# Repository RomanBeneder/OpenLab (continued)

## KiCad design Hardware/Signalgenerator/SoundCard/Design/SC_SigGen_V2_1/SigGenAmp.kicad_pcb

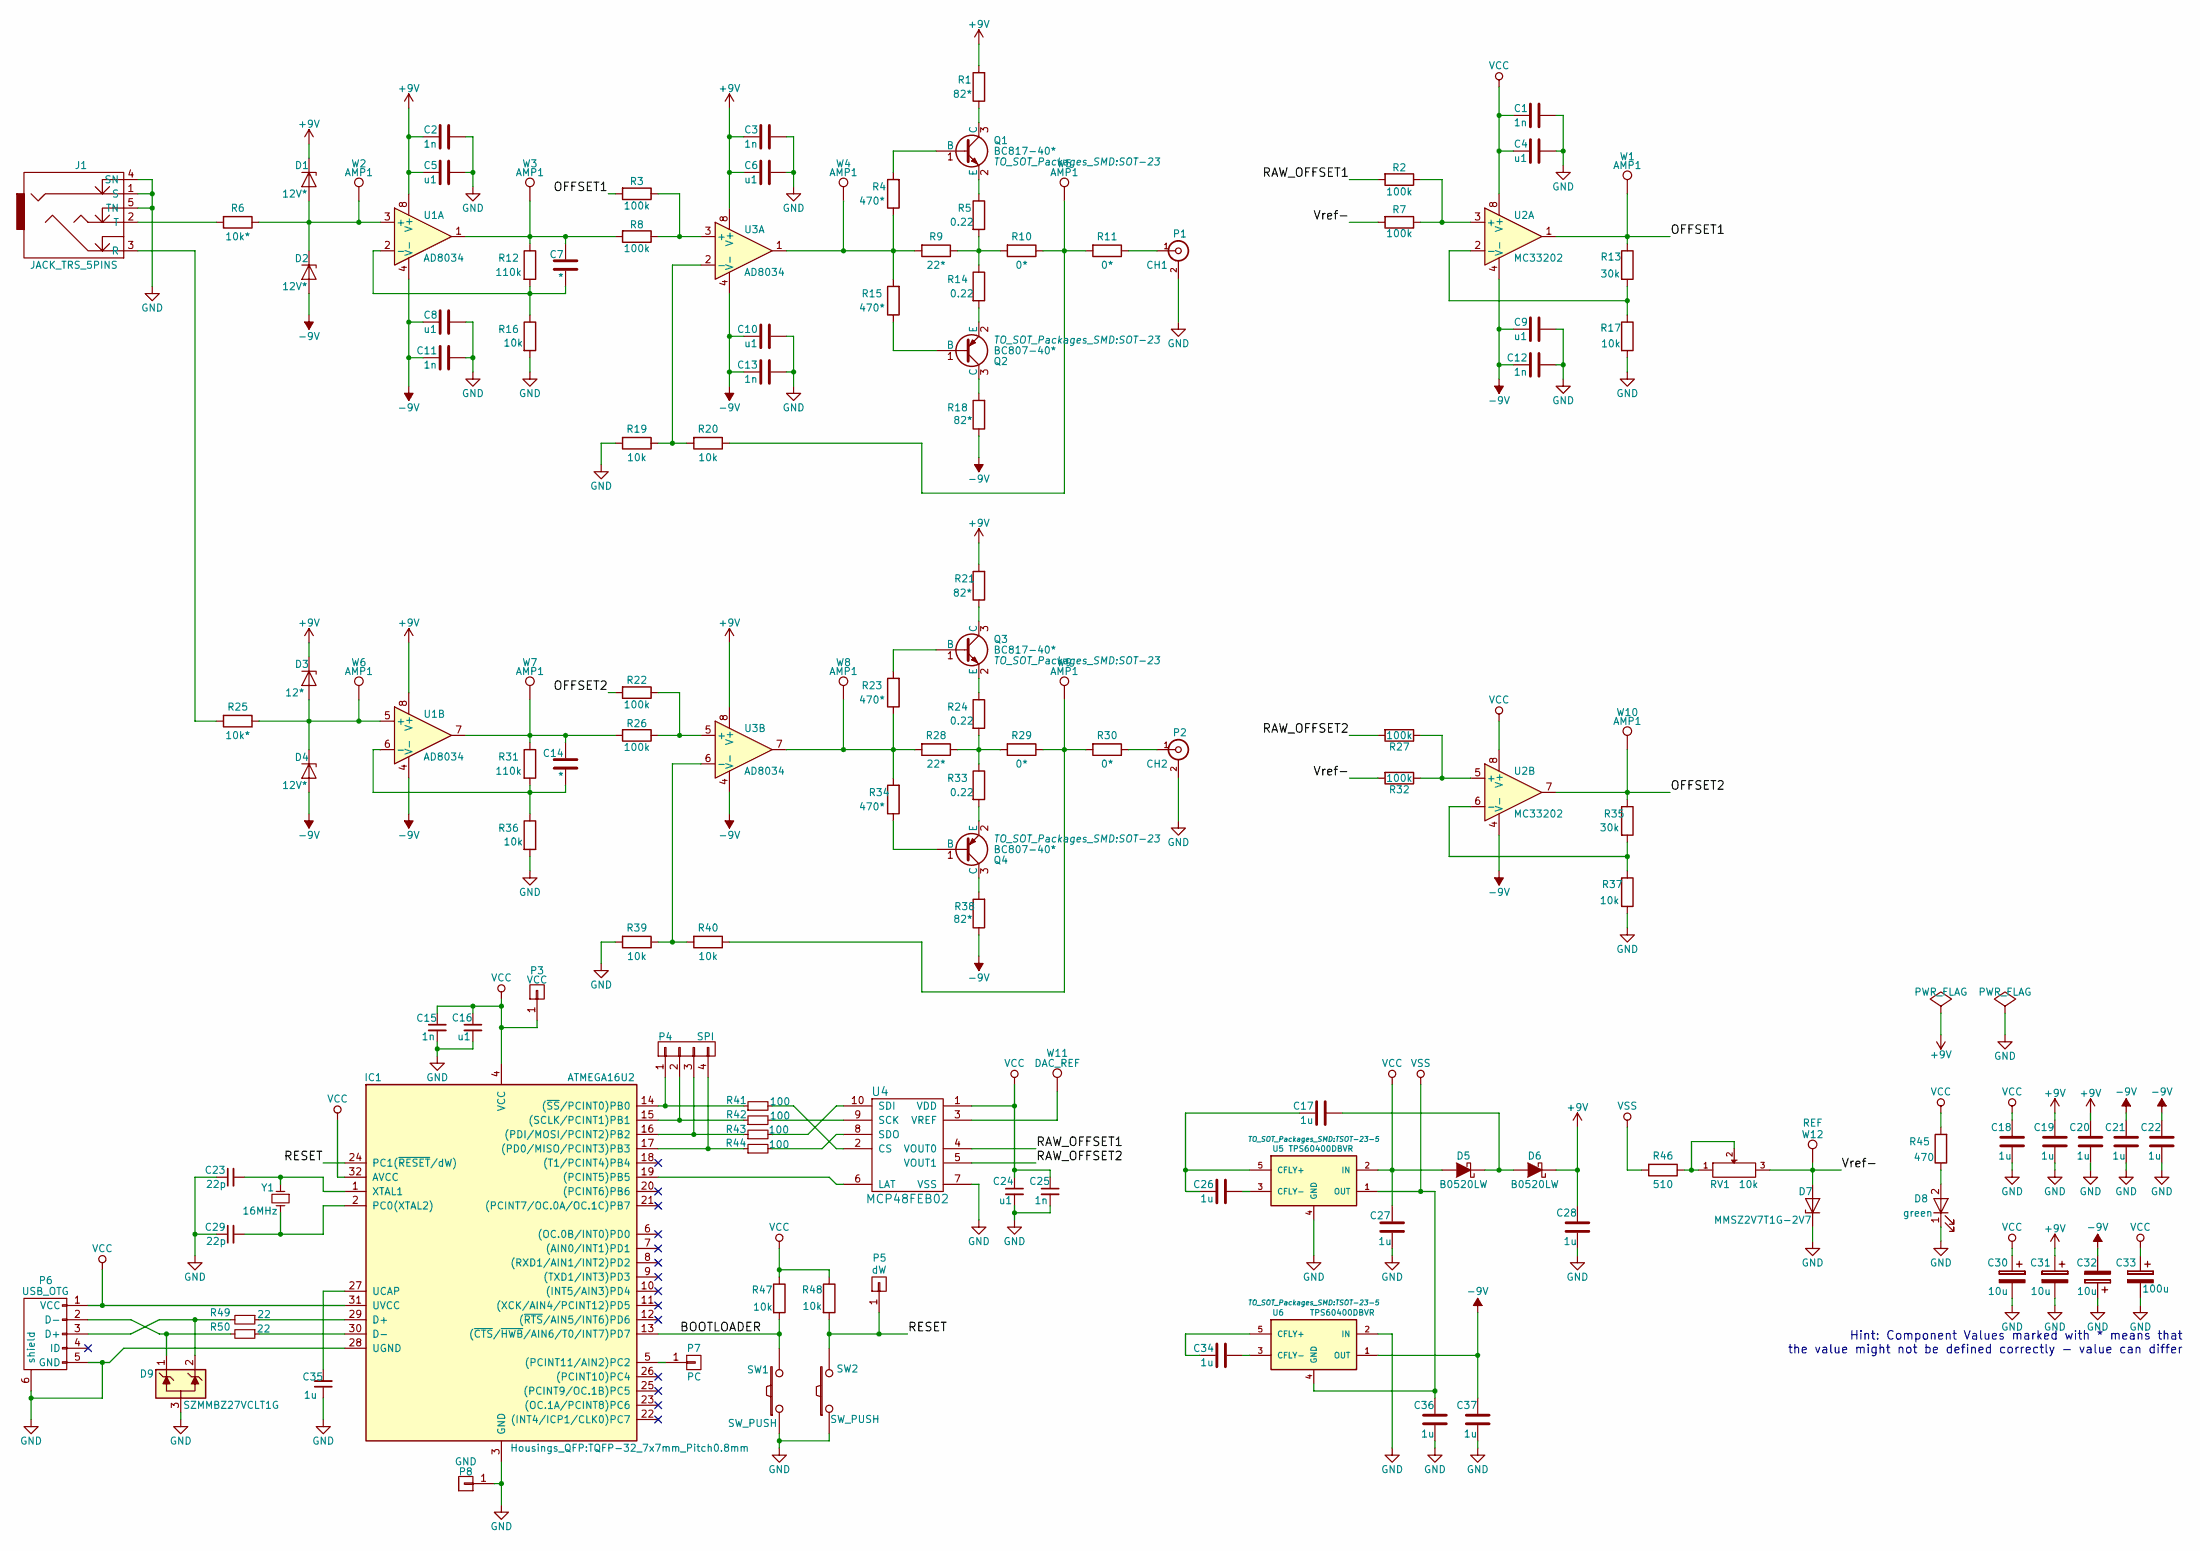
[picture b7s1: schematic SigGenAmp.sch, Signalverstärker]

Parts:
C1, C2, C3, C11, C12, C13, C15, C25: 1n; C_0603
C4, C5, C6, C8, C9, C10, C16, C24: u1; C_0603
C7, C14: *; C_0603
C17, C18, C19, C20, C21, C22, C26, C27, C28, C34, C35, C36, C37: 1u; C_0603
C23, C29: 22p; C_0603
C30, C31, C32: 10u; CP_Elec_4x5.8
C33: 100u; CP_Elec_6.3x7.7
D1, D2, D4: 12V*; D_SOD-323
D3: 12*; D_SOD-323
D5, D6: B0520LW; D_SOD-123
D7: MMSZ2V7T1G-2V7; D_SOD-323F
D8: green; LED_0603
D9: SZMMBZ27VCLT1G; SOT-23
IC1: ATMEGA16U2; TQFP-32_7x7mm_Pitch0.8mm
J1: JACK_TRS_5PINS; TRS3.5mm5PIN
P1: CH1; BNC_Socket_TYCO-AMP_FIX
P2: CH2; BNC_Socket_TYCO-AMP_FIX
P3: VCC; Pin_Header_Straight_1x01_Pitch2.54mm
P4: SPI; Pin_Header_Straight_1x04_Pitch2.54mm
P5: dW; Pin_Header_Straight_1x01_Pitch2.54mm
P6: USB_OTG; USB_Micro-B_SMD
P7: PC; Pin_Header_Straight_1x01_Pitch2.54mm
P8: GND; Pin_Header_Straight_1x01_Pitch2.54mm
Q1, Q3: BC817-40*; SOT-23
Q2, Q4: BC807-40*; SOT-23
R1, R18, R21, R38: 82*; R_1206
R2, R3, R7, R8, R22, R26, R27, R32: 100k; R_0603
R4, R15, R23, R34: 470*; R_0603
R5, R14, R24, R33: 0.22; R_1206
R6, R25: 10k*; R_0603
R9, R28: 22*; R_1206
R10, R11, R29, R30: 0*; R_0603
R12, R31: 110k; R_0603
R13, R35: 30k; R_0603
R16, R17, R19, R20, R36, R37, R39, R40, R47, R48: 10k; R_0603
R41, R42, R43, R44: 100; R_0603
R45: 470; R_0603
R46: 510; R_0603
R49, R50: 22; R_0603
RV1: 10k; Potentiometer_Trimmer-EVM3E
SW1, SW2: SW_PUSH; SW_SPST_PTS645
U1, U3: AD8034; SOIC-8_3.9x4.9mm_Pitch1.27mm
U2: MC33202; SOIC-8_3.9x4.9mm_Pitch1.27mm
U4: MCP48FEB02; MSOP-10_3x3mm_Pitch0.5mm
U5, U6: TPS60400DBVR; TSOT-23-5
W1, W2, W3, W4, W5, W6, W7, W8, W9, W10: AMP1; Measurement_Point_Square-SMD-Pad_Small
W11: DAC_REF; Measurement_Point_Square-SMD-Pad_Small
W12: REF; Measurement_Point_Square-SMD-Pad_Small
Y1: 16MHz; Crystal_SMD_HC49-SD

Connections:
+9V: C2.2, C3.2, C5.2, C6.2, C19.2, C20.2, C28.2, C31.1, D1.1 (K), D3.1 (K), D6.1 (K), R1.2, R21.2, U1.8 (V+), U3.8 (V+)
-9V: C8.2, C9.2, C10.2, C11.2, C12.2, C13.2, C21.2, C22.2, C32.2, C37.2, D2.2 (A), D4.2 (A), R18.1, R38.1, U1.4 (V-), U2.4 (V-), U3.4 (V-), U6.1 (OUT)
/BOOTLOADER: IC1.13 ((~CTS~/~HWB~/AIN6/T0/INT7)PD7), R47.2, SW1.2
/OFFSET1: R3.2, R13.1, U2.1, W1.1
/OFFSET2: R22.2, R35.1, U2.7, W10.1
/RAW_OFFSET1: R2.2, U4.4 (VOUT0)
/RAW_OFFSET2: R27.2, U4.5 (VOUT1)
/RESET: IC1.24 (PC1(~RESET~/dW)), P5.1, R48.2, SW2.2
/Vref-: D7.2 (A), R7.2, R32.2, RV1.3, W12.1
GND: C1.1, C2.1, C3.1, C4.1, C5.1, C6.1, C8.1, C9.1, C10.1, C11.1, C12.1, C13.1, C15.2, C16.2, C18.1, C19.1, C20.1, C21.1, C22.1, C23.1, C24.2, C25.2, C27.1, C28.1, C29.1, C30.2, C31.2, C32.1, C33.2, C35.1, C36.1, C37.1, D7.1 (K), D8.1 (K), D9.3 (A), IC1.3 (GND), IC1.28 (UGND), J1.1 (S), J1.4 (SN), J1.5 (TN), P1.2 (Ext), P2.2 (Ext), P6.5 (GND), P6.6 (shield), P8.1, R16.2, R17.2, R19.2, R36.2, R37.2, R39.2, SW1.1, SW2.1, U4.7 (VSS), U5.4 (GND), U6.2 (IN)
unnamed: C7.1, R12.2, R16.1, U1.2 (-)
unnamed: C7.2, R8.2, R12.1, U1.1, W3.1
unnamed: C14.1, R31.2, R36.1, U1.6 (-)
unnamed: C14.2, R26.2, R31.1, U1.7, W7.1
unnamed: C17.1, D5.1 (K), D6.2 (A)
unnamed: C17.2, C26.2, U5.5 (CFLY+)
unnamed: C23.2, IC1.1 (XTAL1), Y1.1
unnamed: C26.1, U5.3 (CFLY-)
unnamed: C29.2, IC1.2 (PC0(XTAL2)), Y1.2
unnamed: C34.1, U6.3 (CFLY-)
unnamed: C34.2, U6.5 (CFLY+)
unnamed: C35.2, IC1.27 (UCAP)
unnamed: D1.2 (A), D2.1 (K), R6.1, U1.3 (+), W2.1
unnamed: D3.2 (A), D4.1 (K), R25.1, U1.5 (+), W6.1
unnamed: D8.2 (A), R45.1
unnamed: D9.1 (K), P6.2 (D-), R50.2
unnamed: D9.2 (K), P6.3 (D+), R49.2
unnamed: IC1.5 ((PCINT11/AIN2)PC2), P7.1
unnamed: IC1.14 ((~SS~/PCINT0)PB0), P4.1, R41.1
unnamed: IC1.15 ((SCLK/PCINT1)PB1), P4.2, R42.1
unnamed: IC1.16 ((PDI/MOSI/PCINT2)PB2), P4.3, R43.1
unnamed: IC1.17 ((PD0/MISO/PCINT3)PB3), P4.4, R44.1
unnamed: IC1.19 ((PCINT5)PB5), U4.6 (LAT)
unnamed: IC1.29 (D+), R49.1
unnamed: IC1.30 (D-), R50.1
unnamed: J1.2 (T), R6.2
unnamed: J1.3 (R), R25.2
unnamed: P1.1 (In), R11.1
unnamed: P2.1 (In), R30.1
unnamed: Q1.1 (B), R4.2
unnamed: Q1.2 (E), R5.1
unnamed: Q1.3 (C), R1.1
unnamed: Q2.1 (B), R15.1
unnamed: Q2.2 (E), R14.2
unnamed: Q2.3 (C), R18.2
unnamed: Q3.1 (B), R23.2
unnamed: Q3.2 (E), R24.1
unnamed: Q3.3 (C), R21.1
unnamed: Q4.1 (B), R34.1
unnamed: Q4.2 (E), R33.2
unnamed: Q4.3 (C), R38.2
unnamed: R2.1, R7.1, U2.3 (+)
unnamed: R3.1, R8.1, U3.3 (+)
unnamed: R10.1, R11.2, R20.1, W5.1
unnamed: R5.2, R9.1, R10.2, R14.1
unnamed: R13.2, R17.1, U2.2 (-)
unnamed: R4.1, R9.2, R15.2, U3.1, W4.1
unnamed: R19.1, R20.2, U3.2 (-)
unnamed: R22.1, R26.1, U3.5 (+)
unnamed: R23.1, R28.2, R34.2, U3.7, W8.1
unnamed: R24.2, R28.1, R29.2, R33.1
unnamed: R27.1, R32.1, U2.5 (+)
unnamed: R29.1, R30.2, R40.1, W9.1
unnamed: R35.2, R37.1, U2.6 (-)
unnamed: R39.1, R40.2, U3.6 (-)
unnamed: R41.2, U4.2 (CS)
unnamed: R42.2, U4.9 (SCK)
unnamed: R43.2, U4.10 (SDI)
unnamed: R44.2, U4.8 (SDO)
unnamed: R46.1, RV1.1, RV1.2
unnamed: U4.3 (VREF), W11.1
VCC: C1.2, C4.2, C15.1, C16.1, C18.2, C24.1, C25.1, C27.2, C30.1, C33.1, D5.2 (A), IC1.4 (VCC), IC1.31 (UVCC), IC1.32 (AVCC), P3.1, P6.1 (VCC), R45.2, R47.1, R48.1, U2.8 (V+), U4.1 (VDD), U5.2 (IN)
VSS: C36.2, R46.2, U5.1 (OUT), U6.4 (GND)

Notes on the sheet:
Hint: Component Values marked with * means that the value might not be defined correctly - value can differ

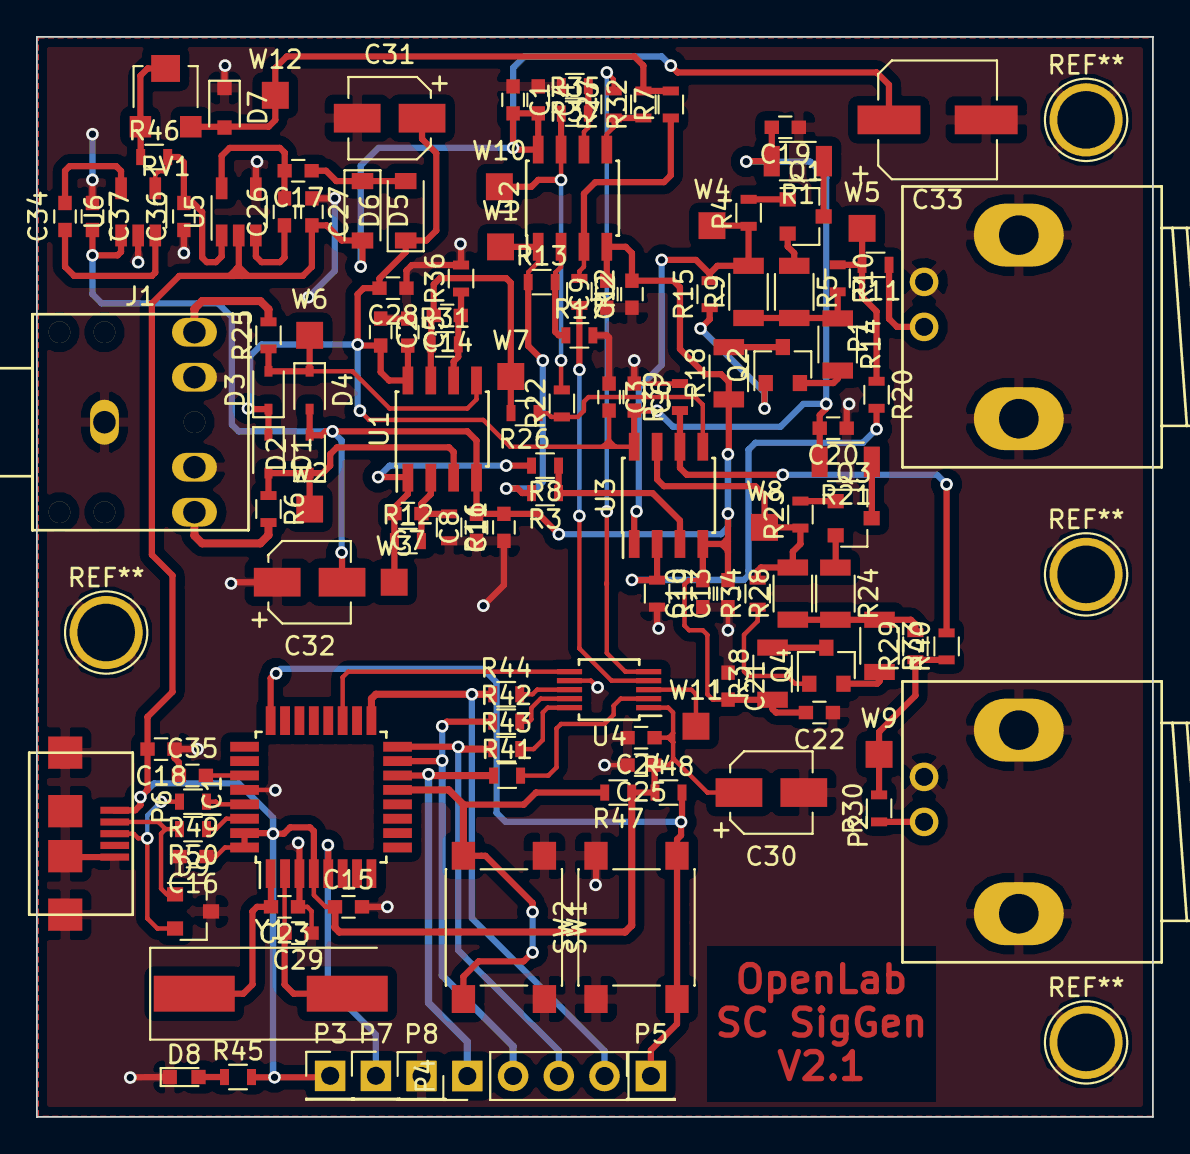
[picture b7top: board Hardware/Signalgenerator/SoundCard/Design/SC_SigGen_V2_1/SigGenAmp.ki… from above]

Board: 2 copper layers, 62.0 x 60.0 mm, 132 parts (0 on the bottom side), 73 nets.

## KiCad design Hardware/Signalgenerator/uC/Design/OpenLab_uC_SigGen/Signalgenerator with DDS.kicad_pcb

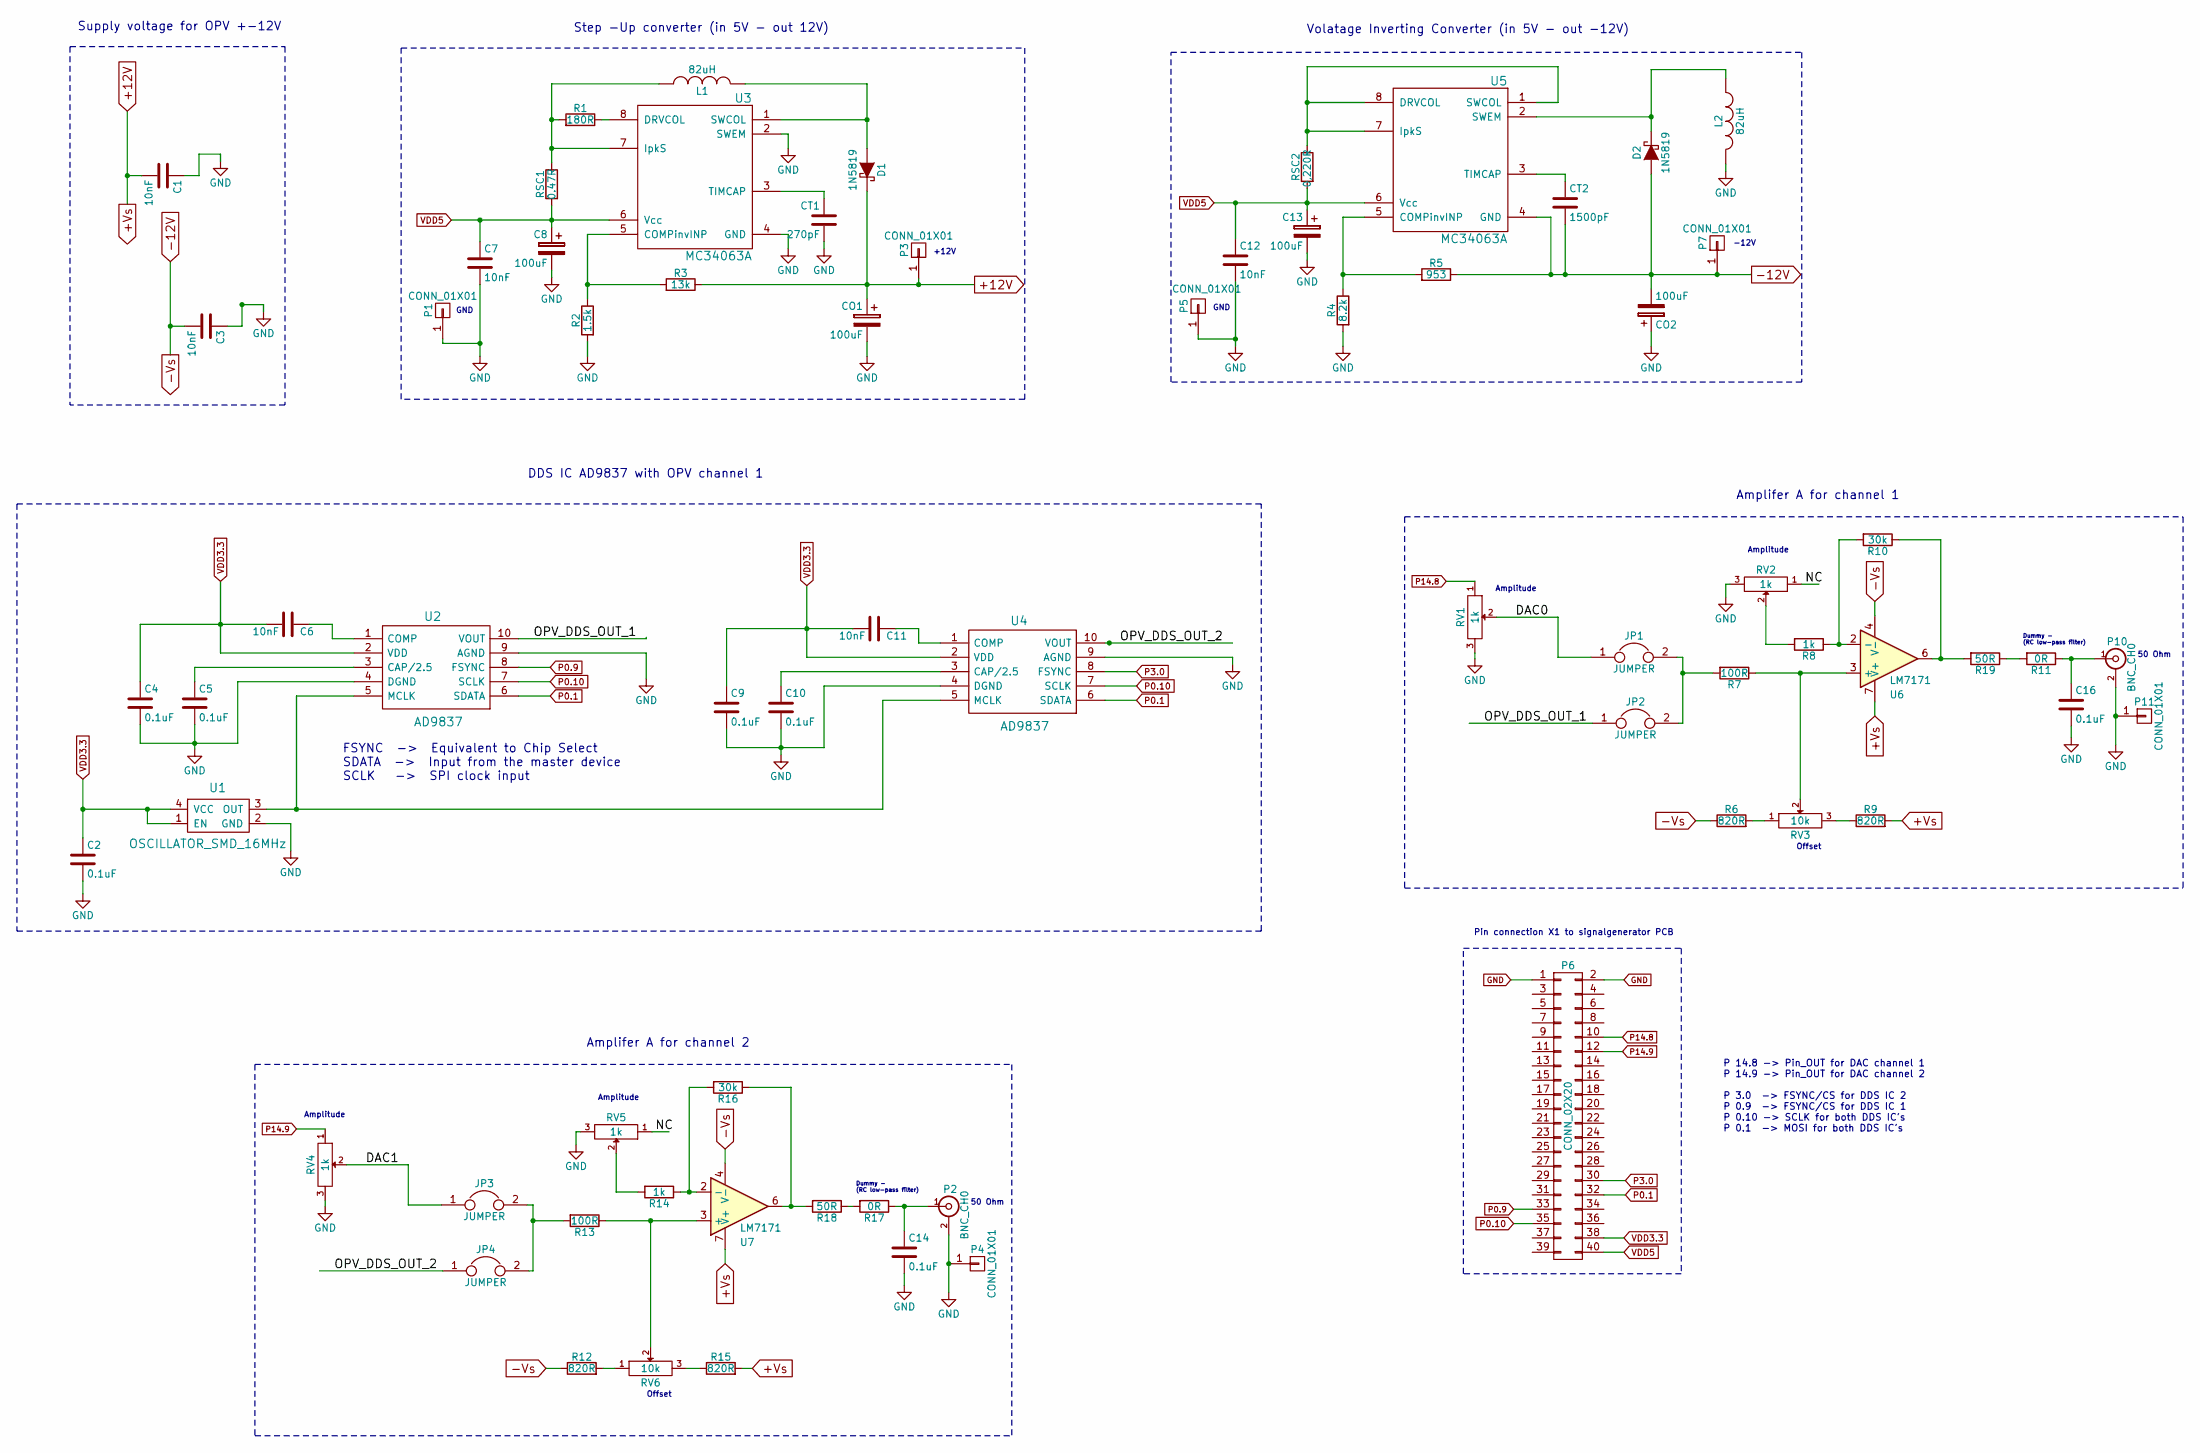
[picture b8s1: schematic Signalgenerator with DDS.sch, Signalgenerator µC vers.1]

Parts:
C1, C3, C6, C7, C11, C12: 10nF; C_0805
C2, C4, C5, C9, C10, C14, C16: 0.1uF; C_0805
C8, C13: 100uF; c_elec_6.3x7.7
CO1, CO2: 100uF; c_elec_6.3x7.7
CT1: 270pF; C_0805
CT2: 1500pF; C_0805
D1, D2: 1N5819; SOD-123
JP1, JP2, JP3, JP4: JUMPER; 2_jumper_2.54mm
L1, L2: 82uH; ELLCTP_inductor
P1, P3, P4, P5, P7, P11: CONN_01X01; SolderWirePad_single_1mmDrill
P2, P10: BNC_CH0; BNC_Socket_TYCO-AMP_LargePads
P6: CONN_02X20; Socket_Strip_Straight_2x20
R1: 180R; R_0805
R2: 1.5k; R_0805
R3: 13k; R_0805
R4: 8.2k; R_0805
R5: 953; R_0805
R6, R9, R12, R15: 820R; R_0805
R7, R13: 100R; R_0805
R8, R14: 1k; R_0805
R10, R16: 30k; R_0805
R11, R17: 0R; R_0805
R18, R19: 50R; R_0805
RSC1: 0.47R; R_0805
RSC2: 0,220R; R_0805
RV1, RV2, RV4, RV5: 1k; trim_bourns_3214w
RV3, RV6: 10k; trim_murata_TS53YL
U1: OSCILLATOR_SMD_16MHz; Oscillator_7_mal_5mm_SMD
U2, U4: AD9837; DFN-10-1EP_3x3mm_Pitch0.5mm
U3, U5: MC34063A; SOIC-8-N
U6, U7: LM7171; SOIC-8_3.9x4.9mm_Pitch1.27mm

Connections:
+12V: C1.2, CO1.1, D1.1 (K), P3.1, R3.1, R9.2, R15.2, U6.7 (V+), U7.7 (V+)
-12V: C3.2, CO2.2, CT2.2, D2.2 (A), P7.1, R5.1, R6.1, R12.1, U5.4 (GND), U6.4 (V-), U7.4 (V-)
/DAC0: JP1.1, RV1.2
/DAC1: JP3.1, RV4.2
/NC: RV2.1, RV5.1
/OPV_DDS_OUT_1: JP2.1, U2.10 (VOUT)
/OPV_DDS_OUT_2: JP4.1, U4.10 (VOUT)
GND: C1.1, C2.2, C3.1, C4.2, C5.2, C7.2, C8.2, C9.2, C10.2, C12.2, C13.2, C14.2, C16.2, CO1.2, CO2.1, CT1.2, L2.1, P1.1, P2.2 (Ext), P4.1, P5.1, P6.1, P6.2, P10.2 (Ext), P11.1, R2.2, R4.2, RV1.3, RV2.3, RV4.3, RV5.3, U1.2 (GND), U2.4 (DGND), U2.9 (AGND), U3.2 (SWEM), U3.4 (GND), U4.4 (DGND), U4.9 (AGND)
unnamed: C5.1, U2.3 (CAP/2.5)
unnamed: C6.1, U2.1 (COMP)
unnamed: C10.1, U4.3 (CAP/2.5)
unnamed: C11.1, U4.1 (COMP)
unnamed: C14.1, P2.1 (In), R17.1
unnamed: C16.1, P10.1 (In), R11.1
unnamed: CT1.1, U3.3 (TIMCAP)
unnamed: CT2.1, U5.3 (TIMCAP)
unnamed: D1.2 (A), L1.1, U3.1 (SWCOL)
unnamed: D2.1 (K), L2.2, U5.2 (SWEM)
unnamed: JP1.2, JP2.2, R7.2
unnamed: JP3.2, JP4.2, R13.2
unnamed: L1.2, R1.2, RSC1.1, U3.7 (IpkS)
unnamed: R1.1, U3.8 (DRVCOL)
unnamed: R2.1, R3.2, U3.5 (COMPinvINP)
unnamed: R4.1, R5.2, U5.5 (COMPinvINP)
unnamed: R6.2, RV3.1
unnamed: R7.1, RV3.2, U6.3 (+)
unnamed: R8.2, RV2.2
unnamed: R9.1, RV3.3
unnamed: R10.1, R19.2, U6.6
unnamed: R8.1, R10.2, U6.2 (-)
unnamed: R11.2, R19.1
unnamed: R12.2, RV6.1
unnamed: R13.1, RV6.2, U7.3 (+)
unnamed: R14.1, R16.2, U7.2 (-)
unnamed: R14.2, RV5.2
unnamed: R15.1, RV6.3
unnamed: R16.1, R18.2, U7.6
unnamed: R17.2, R18.1
unnamed: RSC2.1, U5.1 (SWCOL), U5.7 (IpkS), U5.8 (DRVCOL)
unnamed: U1.3 (OUT), U2.5 (MCLK), U4.5 (MCLK)
P0.1: P6.32, U2.6 (SDATA), U4.6 (SDATA)
P0.9: P6.33, U2.8 (FSYNC)
P0.10: P6.35, U2.7 (SCLK), U4.7 (SCLK)
P3.0: P6.30, U4.8 (FSYNC)
P14.8: P6.10, RV1.1
P14.9: P6.12, RV4.1
VDD3.3: C2.1, C4.1, C6.2, C9.1, C11.2, P6.38, U1.1 (EN), U1.4 (VCC), U2.2 (VDD), U4.2 (VDD)
VDD5: C7.1, C8.1, C12.1, C13.1, P6.40, RSC1.2, RSC2.2, U3.6 (Vcc), U5.6 (Vcc)

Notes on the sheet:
Step -Up converter (in 5V - out 12V)
Volatage Inverting Converter (in 5V - out -12V)
Amplifer A for channel 1
Supply voltage for OPV +-12V
Pin connection X1 to signalgenerator PCB
50 Ohm
FSYNC -> Equivalent to Chip Select SDATA -> Input from the master device SCLK -> SPI clock input
DDS IC AD9837 with OPV channel 1
P 14.8 -> Pin_OUT for DAC channel 1 P 14.9 -> Pin_OUT for DAC channel 2 P 3.0 -> FSYNC/CS for DDS IC 2 P 0.9 -> FSYNC/CS for DDS IC 1 P 0.10 -> SCLK for both DDS IC's P 0.1 -> MOSI for both DDS IC's
Amplitude
Offset
Dummy - (RC low-pass filter)
Amplifer A for channel 2
GND
+12V
-12V

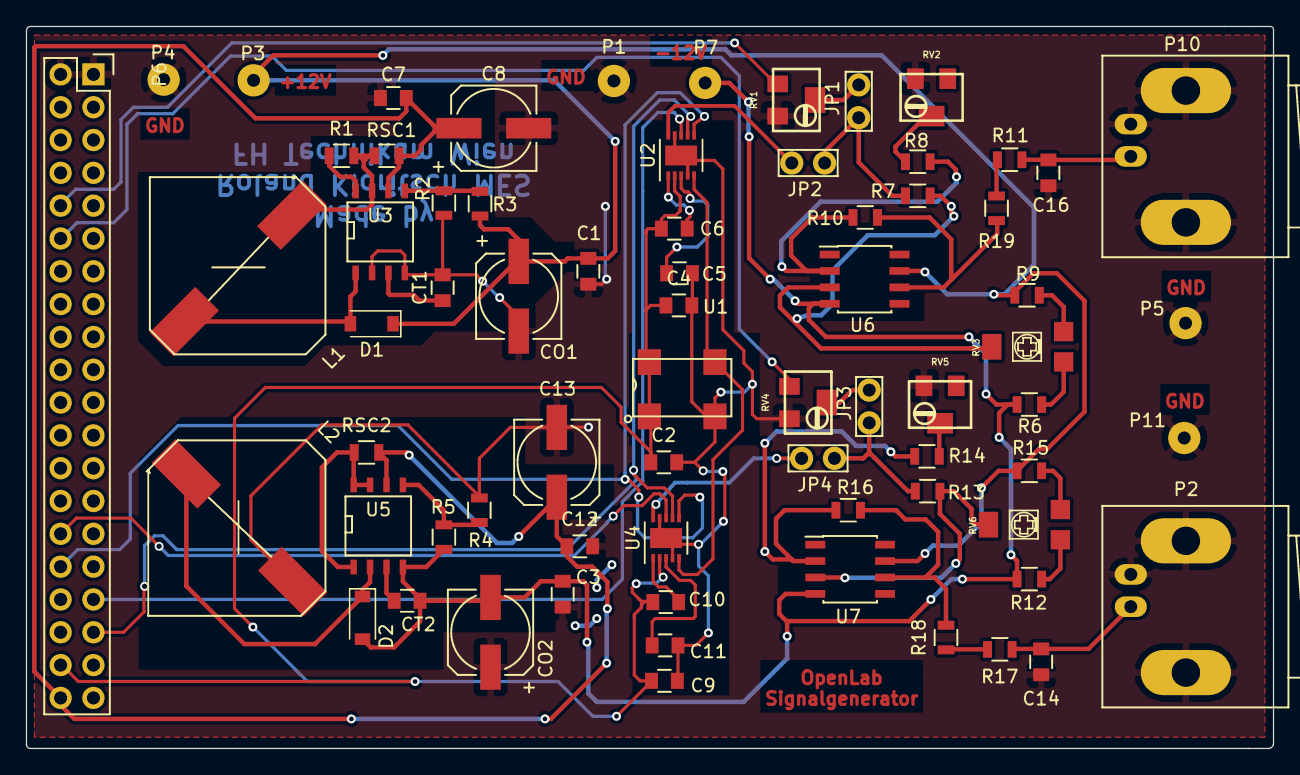
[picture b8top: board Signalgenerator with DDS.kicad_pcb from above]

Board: 2 copper layers, 96.5 x 55.9 mm, 70 parts (0 on the bottom side), 48 nets.

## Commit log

2015-05-11 commited a sorted table of available open-source or commercial uC/FPGA/CPLD/SoundCard-based oscilloscopes
2015-05-11 just a test
2015-05-11 deleted test
2015-05-11 new md commited
2015-05-11 updated md
2015-05-13 deleted survey
2015-10-22 added images to repo
2015-10-22 removed img folder
2015-10-22 created various subsections in the subfolders
2015-10-22 added libusb-1.0 usb bulk transfer example for pc
2015-10-22 pushed example projects for usb bulk transfer on TIVAC and RelaxKit
2015-10-22 added example for various uCs and PC
2015-10-28 added example projects for de0_devboard
2016-11-02 added OpenLab Signaltoolkit install files & directories
2017-03-01 Updated deploy ready software (Launcher, Oscilloscope V1.0.0, Signalgenerator)
2017-03-07 updated OpenLab_SignalToolkit V1
2017-03-20 updated the OpenLab SignalToolkit package to include V2 of the Instruction Manual
2017-03-22 Updated - Oscilloscope Version 1.0.2 - added horizontal positioning function
2017-03-22 edited Readme
2017-03-22 added schematics & layouts for the developed hardware
2017-03-22 removed folders
2017-03-27 renamed SourceCode dir
2017-03-27 renamed Source Code dir
2017-03-27 added source codes for various applications and embedded boards for OpenLab
2017-03-27 adjusted folder structure
2017-03-27 renamed release folder
2017-03-27 deleted OpenLab_Signaltoolkit_V1 folder
2017-05-04 Added Oscilloscope Version 1.0.3
2017-05-04 Added change logs
2017-06-29 Updated Signaltoolkit
2018-03-15 updated binary OpenLab Oscilloscope Java GUI to version 1.1.3 (compatible to V3 and V4 Oscilloscope PCBs) updated binary OpenLab Oscilloscope DE0 IP-Core to version 1.3.2 (Oscilloscope PCB V3) and 1.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
    Source files and Hardware-Design files currently not up-to-date! Will be updated soon.
    Please see the changelog files in the Changelogs folder for further information.
2018-03-15 updated binary OpenLab SignalToolkit launcher application to enable start of future tools --> changed name from SignalToolkit.jar to OpenLab_SignalToolkit_150318.jar (to represent Build_ID) updated t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
    ATTENTION: The OpenLab Multimeter application is currently under development and therefore not included in this update. The Launcher will show a error message if the Multimeter icon is clicked.
2018-04-03 updated OpenLabSignalgenerator.jar updated OpenLab_Signaltoolkit_Application.zip updated OpenLab_SigGen_Changelog.txt
    Changelog:
    OpenLab SigGen Version 20180403_113 - Release
    bugfix - if the external HW was selected the GUI used always the first sound device found
    --> this is generally bad for linux --> changed so the user is able to select the sound device
    in the options menu. The selected device is also saved in a config file.
    bugfix - volume control in linux is not linear! Previous version calculated wrong values for
2018-04-03 OpenLab SigGen Version 20180403_114 - Release
    bugfix - bad implementation of the sound device selection in settings menu
    Device Descriptor could be invalid if only amplitude values in the settings menu were changed
2018-04-24 updated Hardware section - added Multimeter, UI-Source and Logicanalyzer design data renamed OpenLab Signaltoolkit application folder to shorten filename length renamed OpenLab Signaltoolkit .zip fil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
2018-04-24 fixed bad zip file
2018-05-28 Updated Oscilloscope FPGA IP-Core to version 1.3.3 and 1.4.6 Updated Oscilloscope JAVA GUI to version 1.1.4 See the changelog folder for additional information
2018-05-28 Updated design files of the U_I_Source OpenLab Tool - latest version
2018-05-28 added missing note to U_I_Source Hardware folder
2018-05-30 temporary removed Hardware folder for lecture
2018-06-07 added first release version of the OpenLab U-I source Java GUI added Changelogs/OpenLab_U_I_Source_Changelog.txt
2018-09-21 updated all OpenLab tools for preparation of DMS lecture at UAS Technikum Wien (see changelog for more info)
